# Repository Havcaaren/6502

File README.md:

# 8bit CPU

Navrhol som 8-bitový jednoduchý procesor ako záverečný projekt na strednej škole [SPŠE PO](https://www.spse-po.sk/). 
Venujem sa tomuto projektu už šesť mesiacov a výsledkom je procesor s trojicou registrov, 
ROM pamäťou a základnými aritmetickými operáciami (+ a -) a logickými operáciami.

Pre tento procesor som naprogramoval prekladač v jazyku C++. Dokáže preložiť inštrukcie a vyhodnotiť správne adresy skokov.
Napriek tomu, že som navrhoval viac modulov pre RAM a IO registre na ovládanie externých periférií, 
vzhľadom na obmedzený čas a nedostatok integrovaných obvodov, ako napríklad EEPROM pamäť, 
sa mnoho z týchto funkcií zastavilo len na papieri.

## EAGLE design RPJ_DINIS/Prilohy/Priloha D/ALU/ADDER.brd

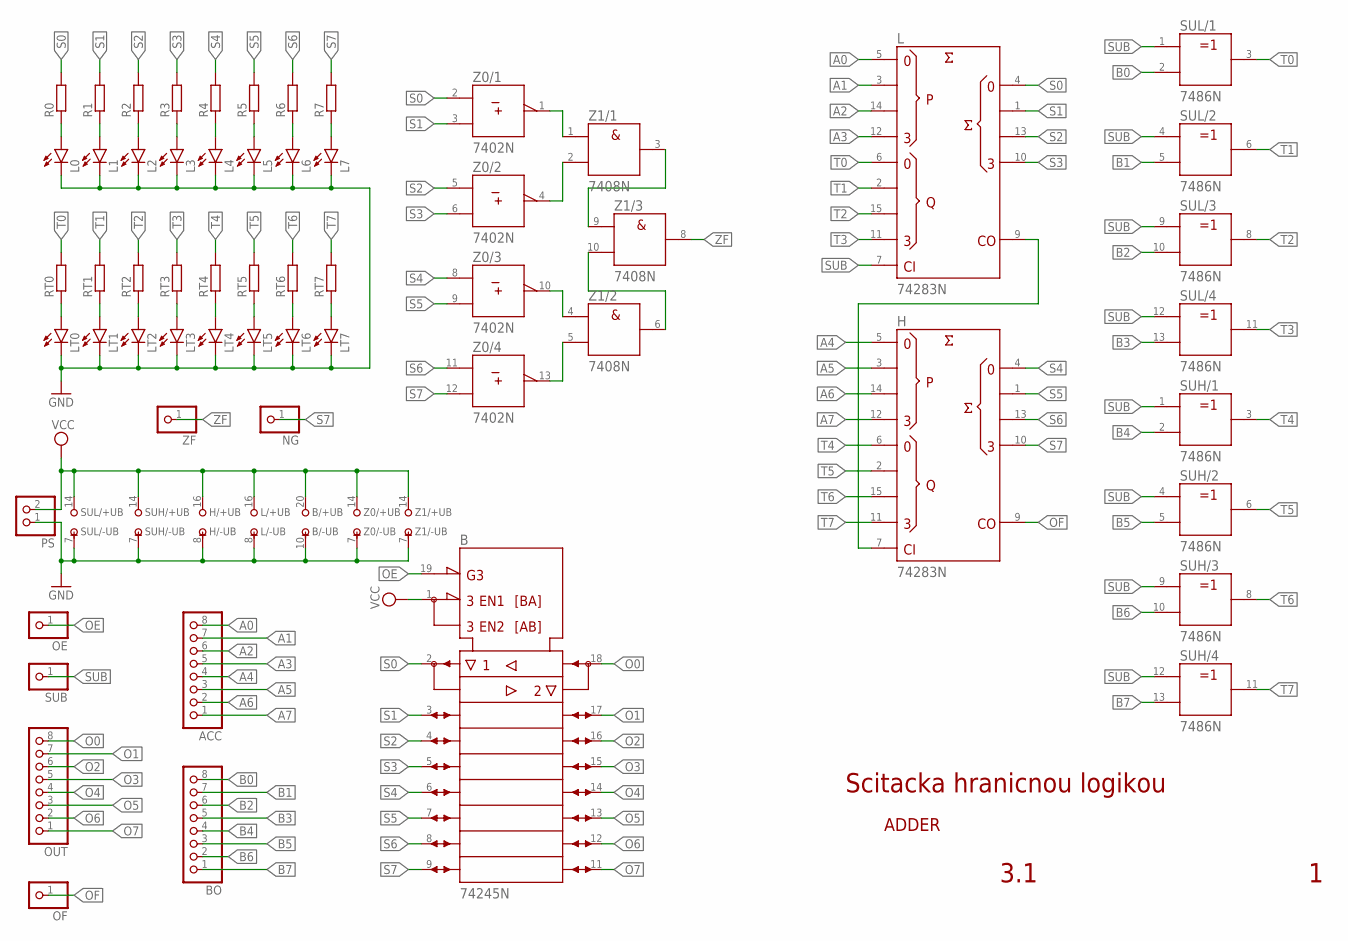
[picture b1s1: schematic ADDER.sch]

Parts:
ACC: PINHD-1X8; 1X08
B: 74245N; DIL20
BO: PINHD-1X8; 1X08
H: 74283N; DIL16
L: 74283N; DIL16
L0, L1, L2, L3, L4, L5, L6, L7: LED5MM
LT0, LT1, LT2, LT3, LT4, LT5, LT6, LT7: LED5MM
NG: PINHD-1X1; 1X01
OE: PINHD-1X1; 1X01
OF: PINHD-1X1; 1X01
OUT: PINHD-1X8; 1X08
PS: PINHD-1X2; 1X02
R0, R1, R2, R3, R4, R5, R6, R7: R-EU_0204/7; 0204/7
RT0, RT1, RT2, RT3, RT4, RT5, RT6, RT7: R-EU_0204/7; 0204/7
SUB: PINHD-1X1; 1X01
SUH: 7486N; DIL14
SUL: 7486N; DIL14
Z0: 7402N; DIL14
Z1: 7408N; DIL14
ZF: PINHD-1X1; 1X01

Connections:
A0: ACC.8, L.5 (A1)
A1: ACC.7, L.3 (A2)
A2: ACC.6, L.14 (A3)
A3: ACC.5, L.12 (A4)
A4: ACC.4, H.5 (A1)
A5: ACC.3, H.3 (A2)
A6: ACC.2, H.14 (A3)
A7: ACC.1, H.12 (A4)
B0: BO.8, SUL.2 (B)
B1: BO.7, SUL.5 (B)
B2: BO.6, SUL.10 (B)
B3: BO.5, SUL.13 (B)
B4: BO.4, SUH.2 (B)
B5: BO.3, SUH.5 (B)
B6: BO.2, SUH.10 (B)
B7: BO.1, SUH.13 (B)
GND: B.10 (-UB), H.8 (-UB), L.8 (-UB), L0.K (C), L1.K (C), L2.K (C), L3.K (C), L4.K (C), L5.K (C), L6.K (C), L7.K (C), LT0.K (C), LT1.K (C), LT2.K (C), LT3.K (C), LT4.K (C), LT5.K (C), LT6.K (C), LT7.K (C), PS.1, SUH.7 (-UB), SUL.7 (-UB), Z0.7 (-UB), Z1.7 (-UB)
unnamed: H.7 (C0), L.9 (C4)
unnamed: L0.A, R0.1
unnamed: L1.A, R1.1
unnamed: L2.A, R2.1
unnamed: L3.A, R3.1
unnamed: L4.A, R4.1
unnamed: L5.A, R5.1
unnamed: L6.A, R6.1
unnamed: L7.A, R7.1
unnamed: Z0.13 (Y), Z1.5 (B)
unnamed: LT0.A, RT0.1
unnamed: Z0.10 (Y), Z1.4 (A)
unnamed: LT1.A, RT1.1
unnamed: Z1.6 (Y), Z1.10 (B)
unnamed: LT2.A, RT2.1
unnamed: LT3.A, RT3.1
unnamed: Z1.3 (Y), Z1.9 (A)
unnamed: LT4.A, RT4.1
unnamed: Z0.4 (Y), Z1.2 (B)
unnamed: LT5.A, RT5.1
unnamed: Z0.1 (Y), Z1.1 (A)
unnamed: LT6.A, RT6.1
unnamed: LT7.A, RT7.1
O0: B.18 (B1), OUT.8
O1: B.17 (B2), OUT.7
O2: B.16 (B3), OUT.6
O3: B.15 (B4), OUT.5
O4: B.14 (B5), OUT.4
O5: B.13 (B6), OUT.3
O6: B.12 (B7), OUT.2
O7: B.11 (B8), OUT.1
OE: B.19 (!G), OE.1
OF: H.9 (C4), OF.1
S0: B.2 (A1), L.4 (S1), R0.2, Z0.2 (A)
S1: B.3 (A2), L.1 (S2), R1.2, Z0.3 (B)
S2: B.4 (A3), L.13 (S3), R2.2, Z0.5 (A)
S3: B.5 (A4), L.10 (S4), R3.2, Z0.6 (B)
S4: B.6 (A5), H.4 (S1), R4.2, Z0.8 (A)
S5: B.7 (A6), H.1 (S2), R5.2, Z0.9 (B)
S6: B.8 (A7), H.13 (S3), R6.2, Z0.11 (A)
S7: B.9 (A8), H.10 (S4), NG.1, R7.2, Z0.12 (B)
SUB: L.7 (C0), SUB.1, SUH.1 (A), SUH.4 (A), SUH.9 (A), SUH.12 (A), SUL.1 (A), SUL.4 (A), SUL.9 (A), SUL.12 (A)
T0: L.6 (B1), RT0.2, SUL.3 (Y)
T1: L.2 (B2), RT1.2, SUL.6 (Y)
T2: L.15 (B3), RT2.2, SUL.8 (Y)
T3: L.11 (B4), RT3.2, SUL.11 (Y)
T4: H.6 (B1), RT4.2, SUH.3 (Y)
T5: H.2 (B2), RT5.2, SUH.6 (Y)
T6: H.15 (B3), RT6.2, SUH.8 (Y)
T7: H.11 (B4), RT7.2, SUH.11 (Y)
VCC: B.1 (DIR), B.20 (+UB), H.16 (+UB), L.16 (+UB), PS.2, SUH.14 (+UB), SUL.14 (+UB), Z0.14 (+UB), Z1.14 (+UB)
ZF: Z1.8 (Y), ZF.1

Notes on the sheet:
Scitacka hranicnou logikou
ADDER
3.1

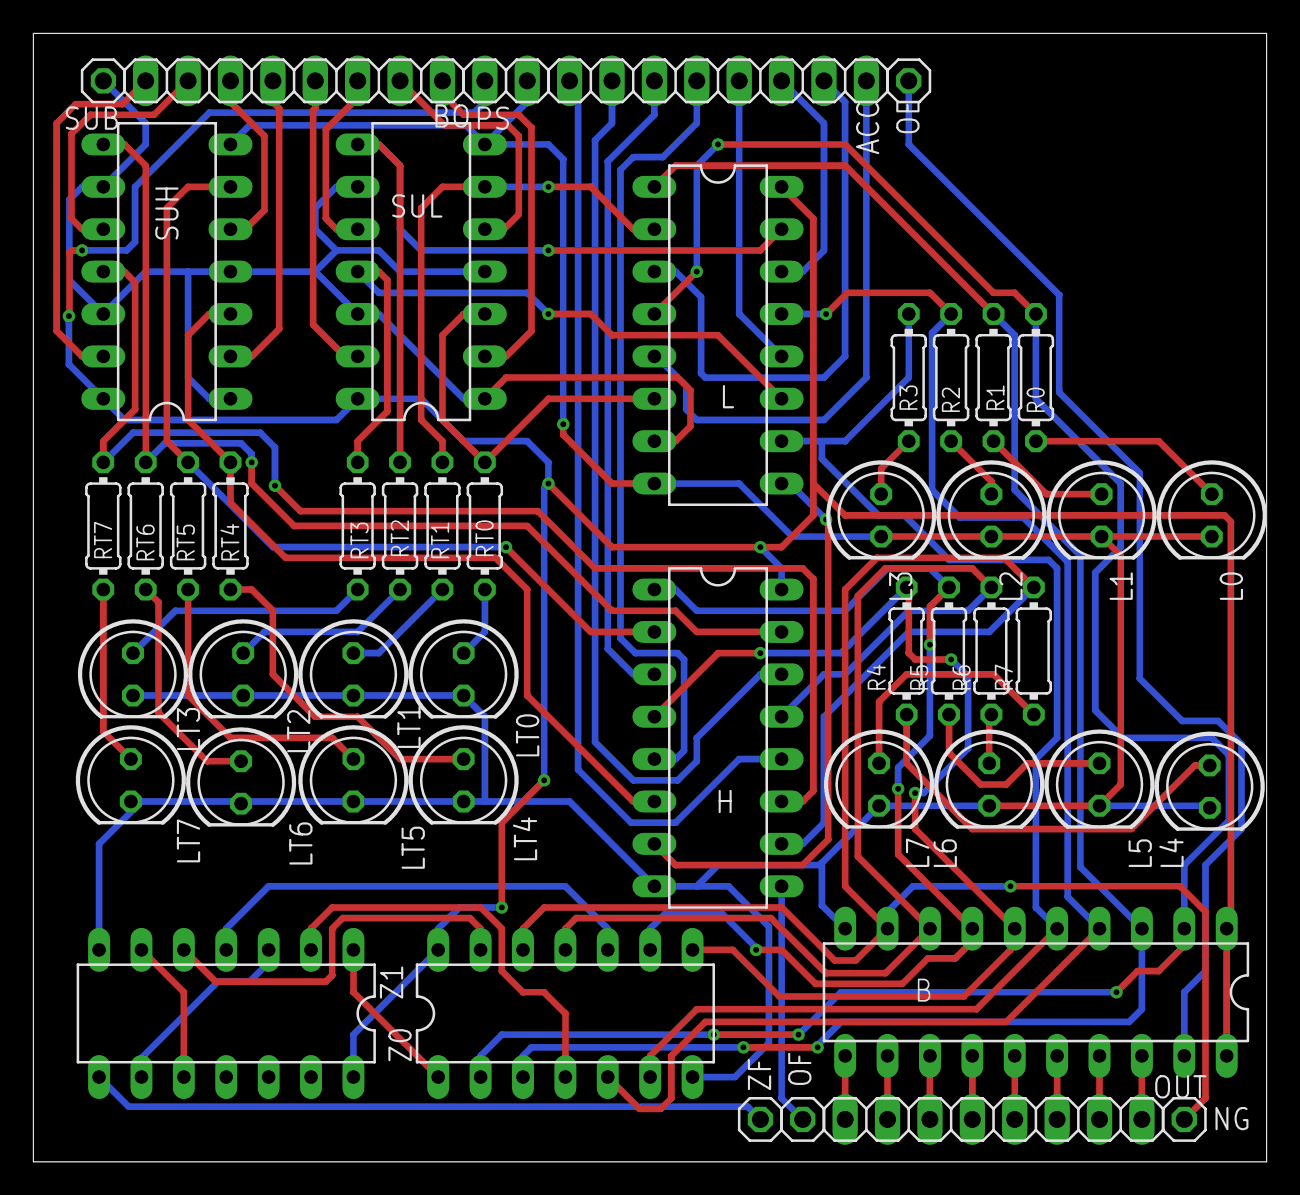
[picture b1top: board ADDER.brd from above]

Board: 2 copper layers, 73.9 x 67.6 mm, 48 parts (0 on the bottom side), 69 nets.

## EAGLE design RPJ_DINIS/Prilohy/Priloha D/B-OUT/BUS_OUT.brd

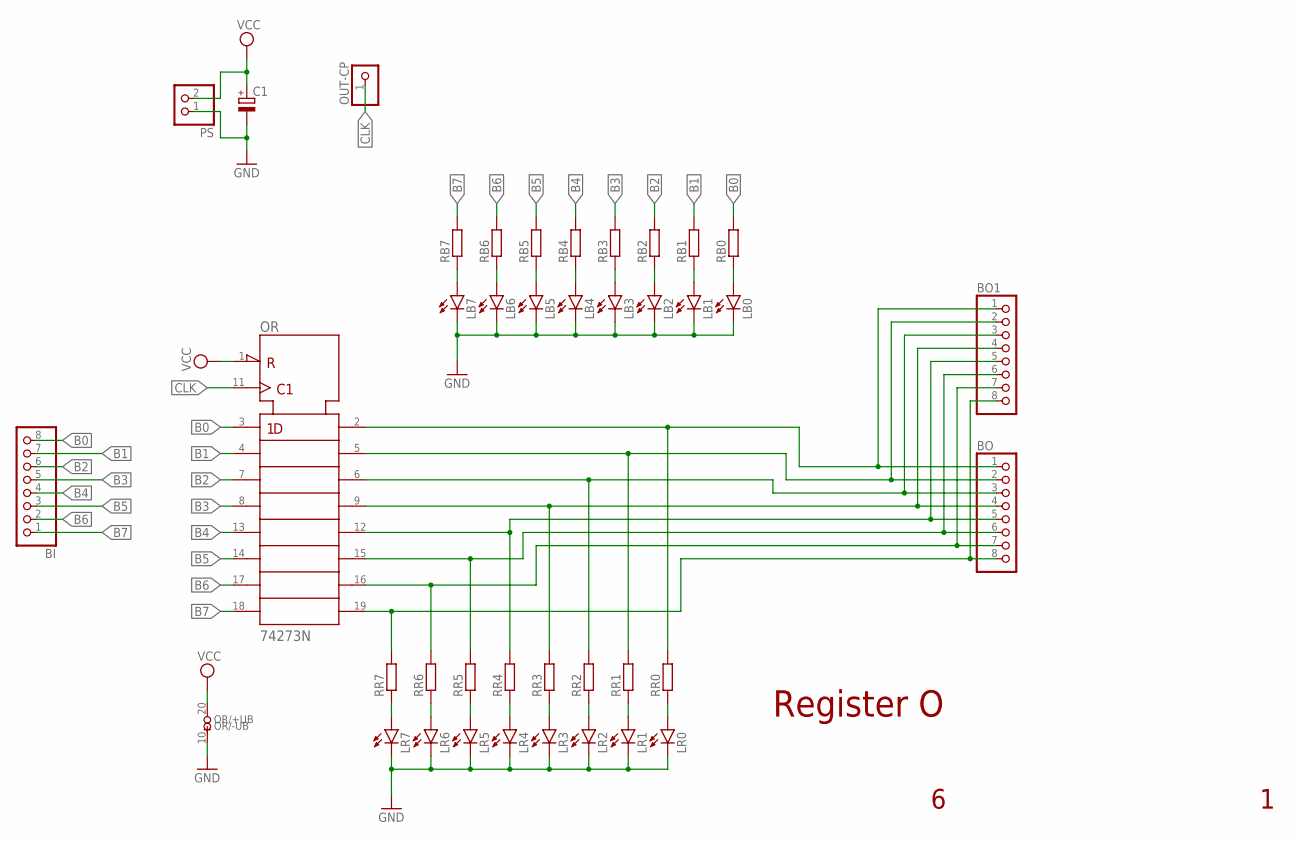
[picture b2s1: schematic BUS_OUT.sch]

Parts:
BI: PINHD-1X8; 1X08
BO, BO1: PINHD-1X8; 1X08
C1: CPOL-EUE2.5-6; E2,5-6
LB0, LB1, LB2, LB3, LB4, LB5, LB6, LB7: LED5MM
LR0, LR1, LR2, LR3, LR4, LR5, LR6, LR7: LED5MM
OR: 74273N; DIL20
OUT-CP: PINHD-1X1; 1X01
PS: PINHD-1X2; 1X02
RB0, RB1, RB2, RB3, RB4, RB5, RB6, RB7: R-EU_0204/7; 0204/7
RR0, RR1, RR2, RR3, RR4, RR5, RR6, RR7: R-EU_0204/7; 0204/7

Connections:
B0: BI.8, OR.3 (1D), RB0.2
B1: BI.7, OR.4 (2D), RB1.2
B2: BI.6, OR.7 (3D), RB2.2
B3: BI.5, OR.8 (4D), RB3.2
B4: BI.4, OR.13 (5D), RB4.2
B5: BI.3, OR.14 (6D), RB5.2
B6: BI.2, OR.17 (7D), RB6.2
B7: BI.1, OR.18 (8D), RB7.2
CLK: OR.11 (CLK), OUT-CP.1
GND: C1.-, LB0.K (C), LB1.K (C), LB2.K (C), LB3.K (C), LB4.K (C), LB5.K (C), LB6.K (C), LB7.K (C), LR0.K (C), LR1.K (C), LR2.K (C), LR3.K (C), LR4.K (C), LR5.K (C), LR6.K (C), LR7.K (C), OR.10 (-UB), PS.1
unnamed: LB7.A, RB7.1
unnamed: LB6.A, RB6.1
unnamed: LB5.A, RB5.1
unnamed: LB4.A, RB4.1
unnamed: LR7.A, RR7.1
unnamed: LB3.A, RB3.1
unnamed: BO.8, BO1.8, OR.19 (8Q), RR7.2
unnamed: LR6.A, RR6.1
unnamed: BO.7, BO1.7, OR.16 (7Q), RR6.2
unnamed: LR5.A, RR5.1
unnamed: LB2.A, RB2.1
unnamed: BO.6, BO1.6, OR.15 (6Q), RR5.2
unnamed: LR4.A, RR4.1
unnamed: BO.5, BO1.5, OR.12 (5Q), RR4.2
unnamed: LR3.A, RR3.1
unnamed: LB1.A, RB1.1
unnamed: BO.4, BO1.4, OR.9 (4Q), RR3.2
unnamed: LR2.A, RR2.1
unnamed: BO.3, BO1.3, OR.6 (3Q), RR2.2
unnamed: LR1.A, RR1.1
unnamed: LB0.A, RB0.1
unnamed: BO.2, BO1.2, OR.5 (2Q), RR1.2
unnamed: LR0.A, RR0.1
unnamed: BO.1, BO1.1, OR.2 (1Q), RR0.2
VCC: C1.+, OR.1 (!CLR), OR.20 (+UB), PS.2

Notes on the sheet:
Register O

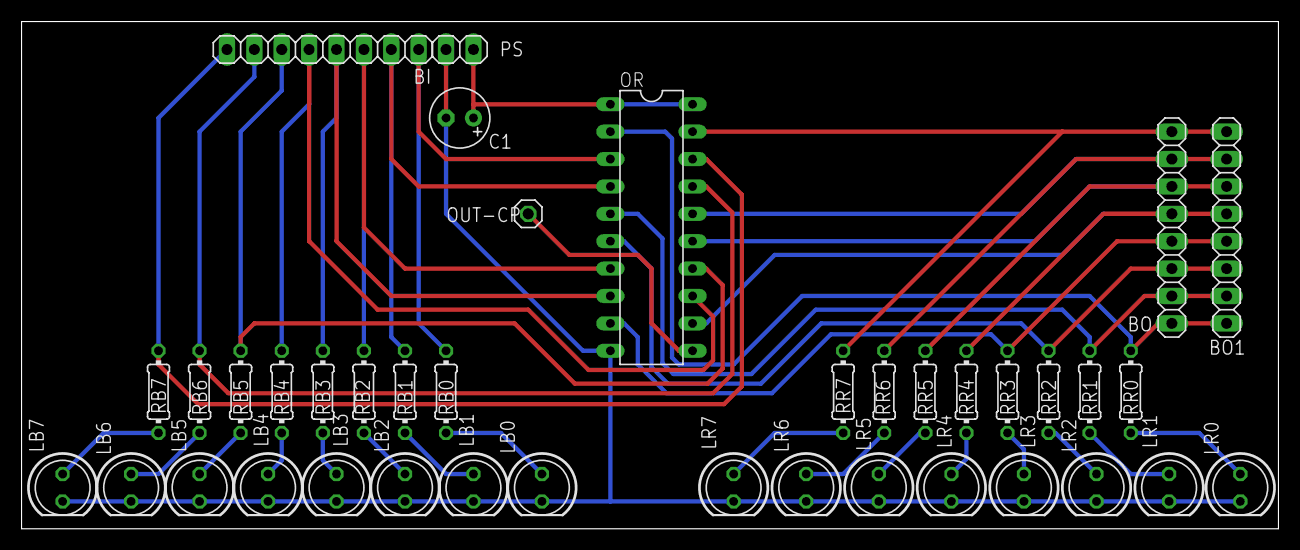
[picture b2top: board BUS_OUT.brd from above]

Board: 2 copper layers, 116.6 x 47.0 mm, 39 parts (0 on the bottom side), 35 nets.

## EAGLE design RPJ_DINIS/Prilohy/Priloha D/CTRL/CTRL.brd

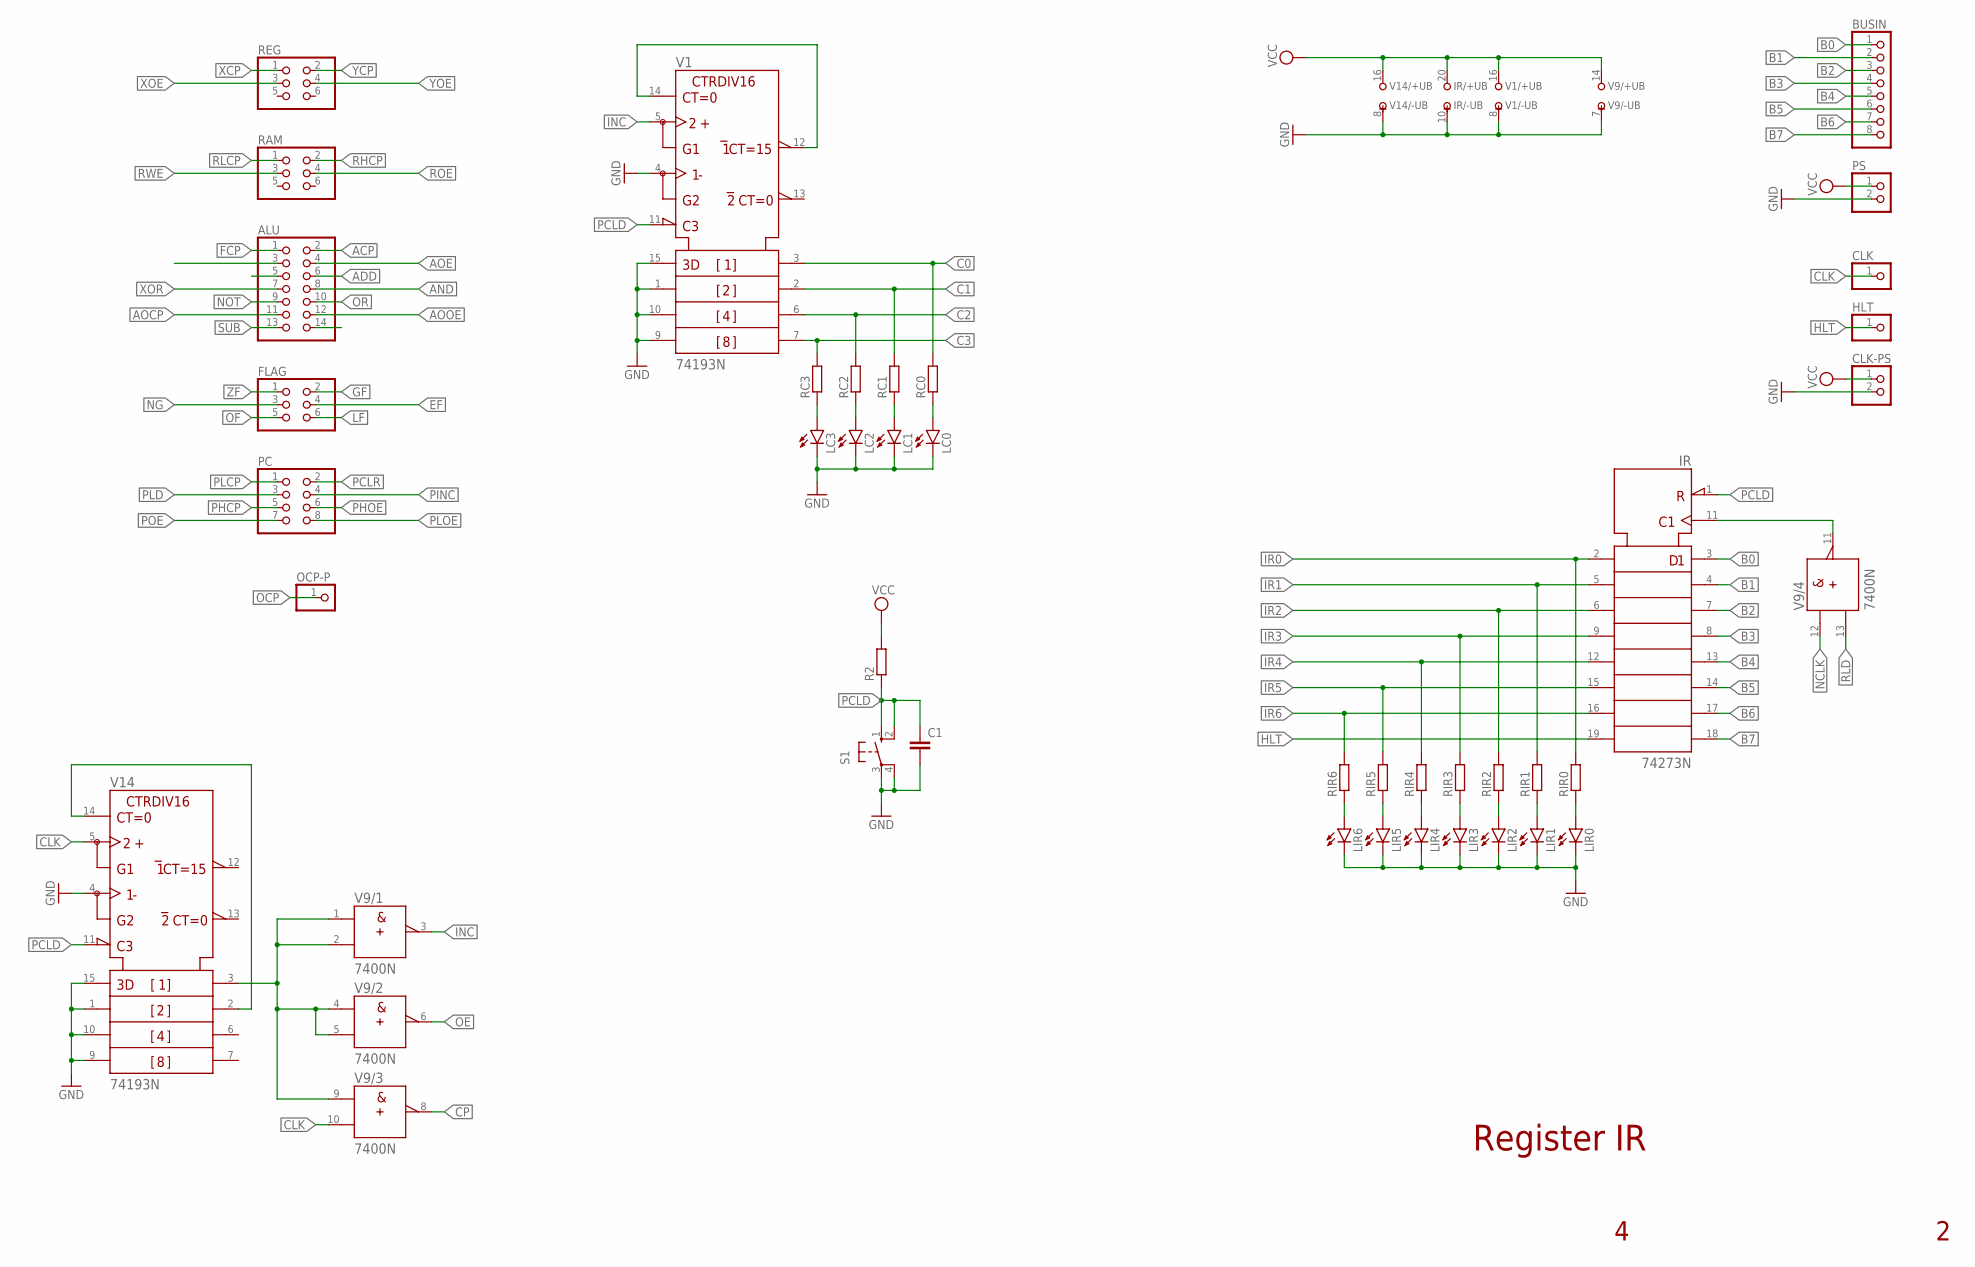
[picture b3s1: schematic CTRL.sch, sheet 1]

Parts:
ALU: PINHD-2X7; 2X07
BUSIN: PINHD-1X8; 1X08
C1: C-EU050-035X075; C050-035X075
CLK: PINHD-1X1; 1X01
CLK-PS: PINHD-1X2; 1X02
FLAG: PINHD-2X3; 2X03
HLT: PINHD-1X1; 1X01
IR: 74273N; DIL20
LC0, LC1, LC2, LC3: LED5MM
LIR0, LIR1, LIR2, LIR3, LIR4, LIR5, LIR6: LED5MM
OCP-P: PINHD-1X1; 1X01
PC: PINHD-2X4; 2X04
PS: PINHD-1X2; 1X02
R2: R-EU_0207/10; 0207/10
RAM: PINHD-2X3; 2X03
RC0, RC1, RC2, RC3: R-EU_0204/7; 0204/7
REG: PINHD-2X3; 2X03
RIR0, RIR1, RIR2, RIR3, RIR4, RIR5, RIR6: R-EU_0204/7; 0204/7
S1: 10-XX; B3F-10XX
V1, V14: 74193N; DIL16
V9: 7400N; DIL14

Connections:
ACP: ALU.2; also elsewhere on the board
ADD: ALU.6; also elsewhere on the board
AND: ALU.8; also elsewhere on the board
AOCP: ALU.11; also elsewhere on the board
AOE: ALU.4; also elsewhere on the board
AOOE: ALU.12; also elsewhere on the board
B0: BUSIN.1, IR.3 (1D)
B1: BUSIN.2, IR.4 (2D)
B2: BUSIN.3, IR.7 (3D)
B3: BUSIN.4, IR.8 (4D)
B4: BUSIN.5, IR.13 (5D)
B5: BUSIN.6, IR.14 (6D)
B6: BUSIN.7, IR.17 (7D)
B7: BUSIN.8, IR.18 (8D)
C0: RC0.2, V1.3 (QA); also elsewhere on the board
C1: RC1.2, V1.2 (QB); also elsewhere on the board
C2: RC2.2, V1.6 (QC); also elsewhere on the board
C3: RC3.2, V1.7 (QD); also elsewhere on the board
CLK: CLK.1, V9.10 (B), V14.5 (UP); also elsewhere on the board
CP: V9.8 (Y); also elsewhere on the board
EF: FLAG.4; also elsewhere on the board
FCP: ALU.1; also elsewhere on the board
GF: FLAG.2; also elsewhere on the board
GND: C1.2, CLK-PS.2, IR.10 (-UB), LC0.K (C), LC1.K (C), LC2.K (C), LC3.K (C), LIR0.K (C), LIR1.K (C), LIR2.K (C), LIR3.K (C), LIR4.K (C), LIR5.K (C), LIR6.K (C), PS.2, S1.3, S1.4 (P1), V1.1 (B), V1.4 (DOWN), V1.8 (-UB), V1.9 (D), V1.10 (C), V1.15 (A), V9.7 (-UB), V14.1 (B), V14.4 (DOWN), V14.8 (-UB), V14.9 (D), V14.10 (C), V14.15 (A); also elsewhere on the board
HLT: HLT.1, IR.19 (8Q)
INC: V1.5 (UP), V9.3 (Y); also elsewhere on the board
IR0: IR.2 (1Q), RIR0.2; also elsewhere on the board
IR1: IR.5 (2Q), RIR1.2; also elsewhere on the board
IR2: IR.6 (3Q), RIR2.2; also elsewhere on the board
IR3: IR.9 (4Q), RIR3.2; also elsewhere on the board
IR4: IR.12 (5Q), RIR4.2; also elsewhere on the board
IR5: IR.15 (6Q), RIR5.2; also elsewhere on the board
IR6: IR.16 (7Q), RIR6.2; also elsewhere on the board
LF: FLAG.6; also elsewhere on the board
unnamed: LC3.A, RC3.1
unnamed: LC2.A, RC2.1
unnamed: LC1.A, RC1.1
unnamed: LC0.A, RC0.1
unnamed: V9.1 (A), V9.2 (B), V9.4 (A), V9.5 (B), V9.9 (A), V14.3 (QA)
unnamed: V14.2 (QB), V14.14 (CLR)
unnamed: V1.12 (!CO), V1.14 (CLR)
unnamed: LIR0.A, RIR0.1
unnamed: LIR1.A, RIR1.1
unnamed: LIR2.A, RIR2.1
unnamed: LIR3.A, RIR3.1
unnamed: LIR4.A, RIR4.1
unnamed: LIR5.A, RIR5.1
unnamed: LIR6.A, RIR6.1
NCLK: V9.12 (A); also elsewhere on the board
NG: FLAG.3; also elsewhere on the board
NOT: ALU.9; also elsewhere on the board
OCP: OCP-P.1; also elsewhere on the board
OE: V9.6 (Y); also elsewhere on the board
OF: FLAG.5; also elsewhere on the board
OR: ALU.10; also elsewhere on the board
PCLD: C1.1, IR.1 (!CLR), R2.1, S1.1 (S), S1.2 (S1), V1.11 (!LOAD), V14.11 (!LOAD)
PCLR: PC.2; also elsewhere on the board
PHCP: PC.5; also elsewhere on the board
PHOE: PC.6; also elsewhere on the board
PINC: PC.4; also elsewhere on the board
PLCP: PC.1; also elsewhere on the board
PLD: PC.3; also elsewhere on the board
PLOE: PC.8; also elsewhere on the board
POE: PC.7; also elsewhere on the board
RHCP: RAM.2; also elsewhere on the board
RL: IR.11 (CLK), V9.11 (Y)
RLCP: RAM.1; also elsewhere on the board
RLD: V9.13 (B); also elsewhere on the board
ROE: RAM.4; also elsewhere on the board
RWE: RAM.3; also elsewhere on the board
SUB: ALU.13; also elsewhere on the board
VCC: CLK-PS.1, IR.20 (+UB), PS.1, R2.2, V1.16 (+UB), V9.14 (+UB), V14.16 (+UB); also elsewhere on the board
XCP: REG.1; also elsewhere on the board
XOE: REG.3; also elsewhere on the board
XOR: ALU.7; also elsewhere on the board
YCP: REG.2; also elsewhere on the board
YOE: REG.4; also elsewhere on the board
ZF: FLAG.1; also elsewhere on the board

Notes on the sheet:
Register IR

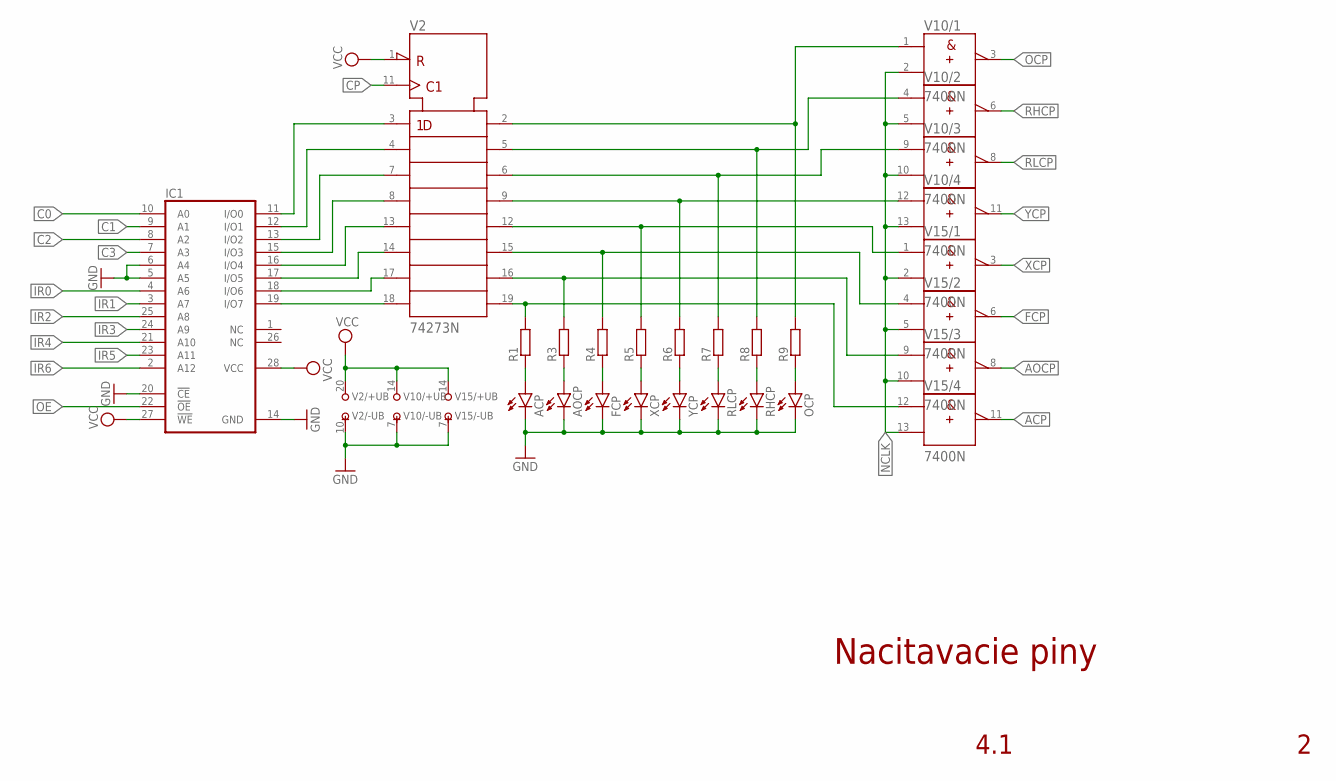
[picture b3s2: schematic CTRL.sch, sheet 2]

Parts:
ACP: LED5MM
AOCP: LED5MM
FCP: LED5MM
IC1: 28C64C; DIL28-6
OCP: LED5MM
R1, R3, R4, R5, R6, R7, R8, R9: R-EU_0204/7; 0204/7
RHCP: LED5MM
RLCP: LED5MM
V2: 74273N; DIL20
V10, V15: 7400N; DIL14
XCP: LED5MM
YCP: LED5MM

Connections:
ACP: V15.11 (Y); also elsewhere on the board
ACP0: IC1.11 (I/O0), V2.3 (1D)
ACP00: R9.2, V2.2 (1Q), V10.1 (A)
ADD0: IC1.17 (I/O5), V2.14 (6D)
ADD00: R4.2, V2.15 (6Q), V15.4 (A)
AND0: IC1.19 (I/O7), V2.18 (8D)
AND00: R1.2, V2.19 (8Q), V15.12 (A)
AOCP: V15.8 (Y); also elsewhere on the board
AOCP0: IC1.15 (I/O3), V2.8 (4D)
AOCP00: R6.2, V2.9 (4Q), V10.12 (A)
AOE0: IC1.12 (I/O1), V2.4 (2D)
AOE00: R8.2, V2.5 (2Q), V10.4 (A)
AOOE0: IC1.16 (I/O4), V2.13 (5D)
AOOE00: R5.2, V2.12 (5Q), V15.1 (A)
C0: IC1.10 (A0); also elsewhere on the board
C1: IC1.9 (A1); also elsewhere on the board
C2: IC1.8 (A2); also elsewhere on the board
C3: IC1.7 (A3); also elsewhere on the board
CP: V2.11 (CLK); also elsewhere on the board
FCP: V15.6 (Y); also elsewhere on the board
FCP0: IC1.13 (I/O2), V2.7 (3D)
FCP00: R7.2, V2.6 (3Q), V10.9 (A)
GND: ACP.K (C), AOCP.K (C), FCP.K (C), IC1.5 (A5), IC1.6 (A4), IC1.14 (GND), IC1.20 (!CE), OCP.K (C), RHCP.K (C), RLCP.K (C), V2.10 (-UB), V10.7 (-UB), V15.7 (-UB), XCP.K (C), YCP.K (C); also elsewhere on the board
IR0: IC1.4 (A6); also elsewhere on the board
IR1: IC1.3 (A7); also elsewhere on the board
IR2: IC1.25 (A8); also elsewhere on the board
IR3: IC1.24 (A9); also elsewhere on the board
IR4: IC1.21 (A10); also elsewhere on the board
IR5: IC1.23 (A11); also elsewhere on the board
IR6: IC1.2 (A12); also elsewhere on the board
unnamed: ACP.A, R1.1
unnamed: AOCP.A, R3.1
unnamed: FCP.A, R4.1
unnamed: R5.1, XCP.A
unnamed: R6.1, YCP.A
unnamed: R7.1, RLCP.A
unnamed: R8.1, RHCP.A
unnamed: OCP.A, R9.1
NCLK: V10.2 (B), V10.5 (B), V10.10 (B), V10.13 (B), V15.2 (B), V15.5 (B), V15.10 (B), V15.13 (B); also elsewhere on the board
OCP: V10.3 (Y); also elsewhere on the board
OE: IC1.22 (!OE); also elsewhere on the board
RHCP: V10.6 (Y); also elsewhere on the board
RLCP: V10.8 (Y); also elsewhere on the board
SUB0: IC1.18 (I/O6), V2.17 (7D)
SUB00: R3.2, V2.16 (7Q), V15.9 (A)
VCC: IC1.27 (!WE), IC1.28 (VCC), V2.1 (!CLR), V2.20 (+UB), V10.14 (+UB), V15.14 (+UB); also elsewhere on the board
XCP: V15.3 (Y); also elsewhere on the board
YCP: V10.11 (Y); also elsewhere on the board

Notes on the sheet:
4.1
Nacitavacie piny

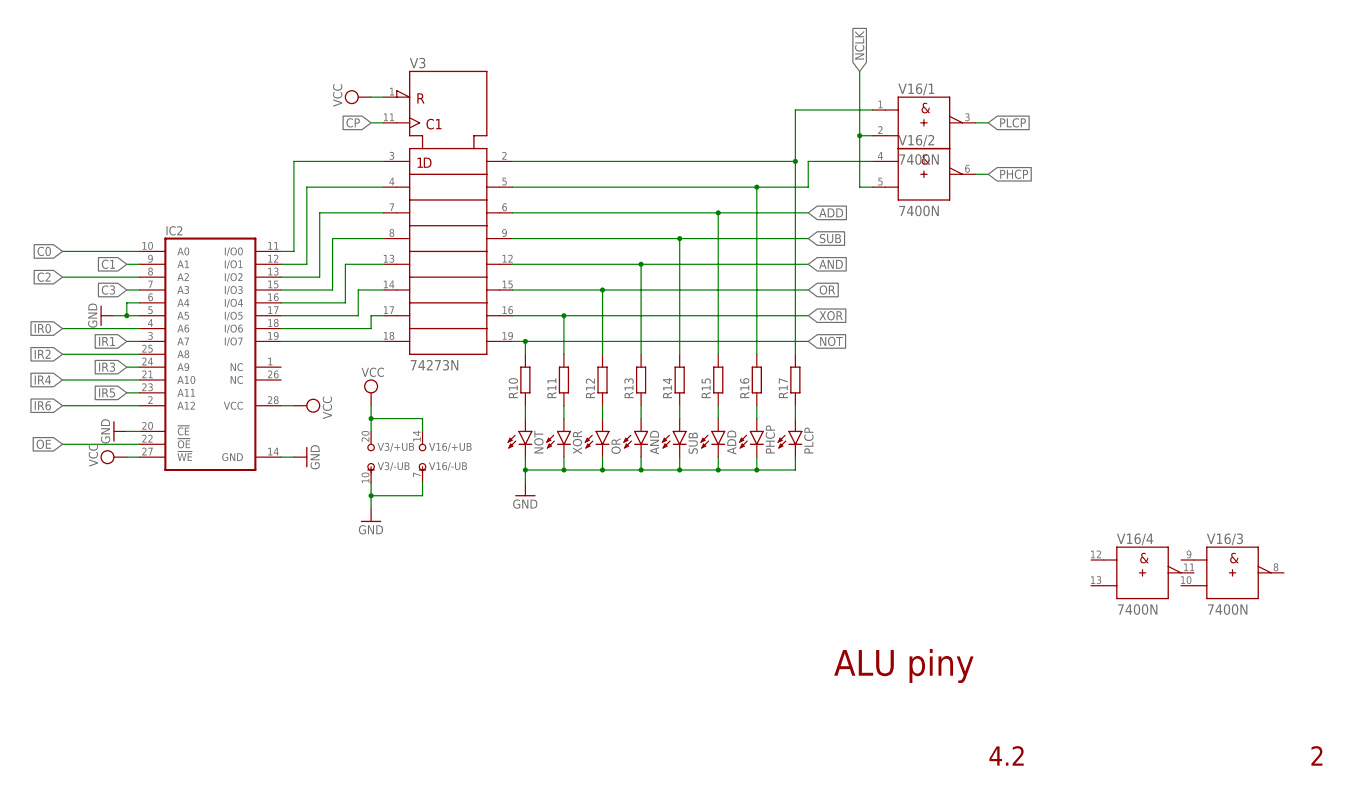
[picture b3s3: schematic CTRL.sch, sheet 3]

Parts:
ADD: LED5MM
AND: LED5MM
IC2: 28C64C; DIL28-6
NOT: LED5MM
OR: LED5MM
PHCP: LED5MM
PLCP: LED5MM
R10, R11, R12, R13, R14, R15, R16, R17: R-EU_0204/7; 0204/7
SUB: LED5MM
V3: 74273N; DIL20
V16: 7400N; DIL14
XOR: LED5MM

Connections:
ADD: R15.2, V3.6 (3Q); also elsewhere on the board
AND: R13.2, V3.12 (5Q); also elsewhere on the board
C0: IC2.10 (A0); also elsewhere on the board
C1: IC2.9 (A1); also elsewhere on the board
C2: IC2.8 (A2); also elsewhere on the board
C3: IC2.7 (A3); also elsewhere on the board
CP: V3.11 (CLK); also elsewhere on the board
GND: ADD.K (C), AND.K (C), IC2.5 (A5), IC2.6 (A4), IC2.14 (GND), IC2.20 (!CE), NOT.K (C), OR.K (C), PHCP.K (C), PLCP.K (C), SUB.K (C), V3.10 (-UB), V16.7 (-UB), XOR.K (C); also elsewhere on the board
IR0: IC2.4 (A6); also elsewhere on the board
IR1: IC2.3 (A7); also elsewhere on the board
IR2: IC2.25 (A8); also elsewhere on the board
IR3: IC2.24 (A9); also elsewhere on the board
IR4: IC2.21 (A10); also elsewhere on the board
IR5: IC2.23 (A11); also elsewhere on the board
IR6: IC2.2 (A12); also elsewhere on the board
unnamed: NOT.A, R10.1
unnamed: R11.1, XOR.A
unnamed: OR.A, R12.1
unnamed: AND.A, R13.1
unnamed: R14.1, SUB.A
unnamed: ADD.A, R15.1
unnamed: PHCP.A, R16.1
unnamed: PLCP.A, R17.1
NCLK: V16.2 (B), V16.5 (B); also elsewhere on the board
NOT: R10.2, V3.19 (8Q); also elsewhere on the board
NOT0: IC2.13 (I/O2), V3.7 (3D)
OE: IC2.22 (!OE); also elsewhere on the board
OR: R12.2, V3.15 (6Q); also elsewhere on the board
OR0: IC2.11 (I/O0), V3.3 (1D)
OR00: R17.2, V3.2 (1Q), V16.1 (A)
PHCP: V16.6 (Y); also elsewhere on the board
PHCP0: IC2.16 (I/O4), V3.13 (5D)
PHOE0: IC2.18 (I/O6), V3.17 (7D)
PINC0: IC2.19 (I/O7), V3.18 (8D)
PLCP: V16.3 (Y); also elsewhere on the board
PLCP0: IC2.15 (I/O3), V3.8 (4D)
PLOE0: IC2.17 (I/O5), V3.14 (6D)
SUB: R14.2, V3.9 (4Q); also elsewhere on the board
VCC: IC2.27 (!WE), IC2.28 (VCC), V3.1 (!CLR), V3.20 (+UB), V16.14 (+UB); also elsewhere on the board
XOR: R11.2, V3.16 (7Q); also elsewhere on the board
XOR0: IC2.12 (I/O1), V3.4 (2D)
XOR00: R16.2, V3.5 (2Q), V16.4 (A)

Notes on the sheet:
4.2
ALU piny

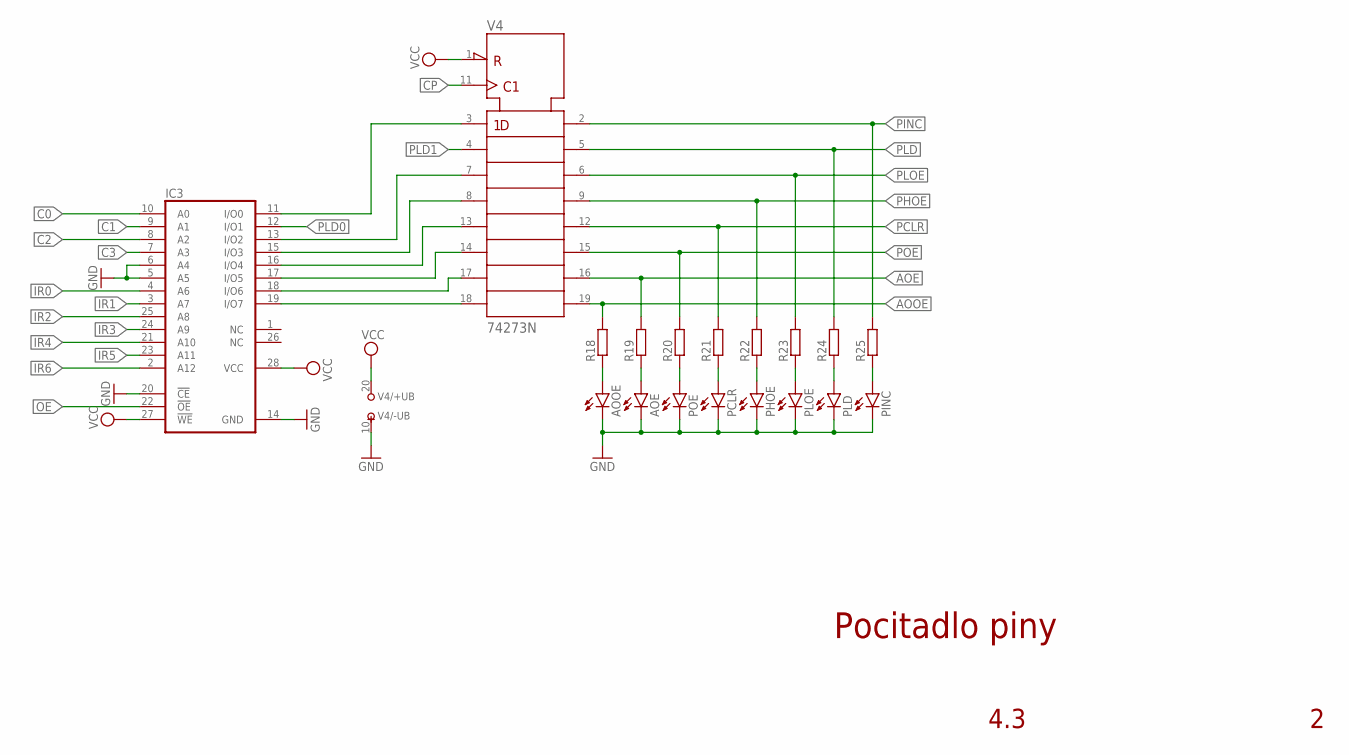
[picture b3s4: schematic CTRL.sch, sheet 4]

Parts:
AOE: LED5MM
AOOE: LED5MM
IC3: 28C64C; DIL28-6
PCLR: LED5MM
PHOE: LED5MM
PINC: LED5MM
PLD: LED5MM
PLOE: LED5MM
POE: LED5MM
R18, R19, R20, R21, R22, R23, R24, R25: R-EU_0204/7; 0204/7
V4: 74273N; DIL20

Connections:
AOE: R19.2, V4.16 (7Q); also elsewhere on the board
AOOE: R18.2, V4.19 (8Q); also elsewhere on the board
C0: IC3.10 (A0); also elsewhere on the board
C1: IC3.9 (A1); also elsewhere on the board
C2: IC3.8 (A2); also elsewhere on the board
C3: IC3.7 (A3); also elsewhere on the board
CP: V4.11 (CLK); also elsewhere on the board
GND: AOE.K (C), AOOE.K (C), IC3.5 (A5), IC3.6 (A4), IC3.14 (GND), IC3.20 (!CE), PCLR.K (C), PHOE.K (C), PINC.K (C), PLD.K (C), PLOE.K (C), POE.K (C), V4.10 (-UB); also elsewhere on the board
IR0: IC3.4 (A6); also elsewhere on the board
IR1: IC3.3 (A7); also elsewhere on the board
IR2: IC3.25 (A8); also elsewhere on the board
IR3: IC3.24 (A9); also elsewhere on the board
IR4: IC3.21 (A10); also elsewhere on the board
IR5: IC3.23 (A11); also elsewhere on the board
IR6: IC3.2 (A12); also elsewhere on the board
unnamed: AOOE.A, R18.1
unnamed: AOE.A, R19.1
unnamed: POE.A, R20.1
unnamed: PCLR.A, R21.1
unnamed: PHOE.A, R22.1
unnamed: PLOE.A, R23.1
unnamed: PLD.A, R24.1
unnamed: PINC.A, R25.1
OCP0: IC3.19 (I/O7), V4.18 (8D)
OE: IC3.22 (!OE); also elsewhere on the board
PCLR: R21.2, V4.12 (5Q); also elsewhere on the board
PCLR0: IC3.11 (I/O0), V4.3 (1D)
PHOE: R22.2, V4.9 (4Q); also elsewhere on the board
PINC: R25.2, V4.2 (1Q); also elsewhere on the board
PLD: R24.2, V4.5 (2Q); also elsewhere on the board
PLD0: IC3.12 (I/O1); also elsewhere on the board
PLD1: V4.4 (2D); also elsewhere on the board
PLOE: R23.2, V4.6 (3Q); also elsewhere on the board
POE: R20.2, V4.15 (6Q); also elsewhere on the board
POE0: IC3.13 (I/O2), V4.7 (3D)
RHCP0: IC3.16 (I/O4), V4.13 (5D)
RLCP0: IC3.15 (I/O3), V4.8 (4D)
ROE0: IC3.18 (I/O6), V4.17 (7D)
RWE0: IC3.17 (I/O5), V4.14 (6D)
VCC: IC3.27 (!WE), IC3.28 (VCC), V4.1 (!CLR), V4.20 (+UB); also elsewhere on the board

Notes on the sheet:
4.3
Pocitadlo piny
